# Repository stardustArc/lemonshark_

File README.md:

# lemonshark

a wireless split keyboard with per-key RGB and nice!view displays

---
## to do
- [ ] write readme (this is gonna take a lot of commits lol)
- [ ] upload images/gallery
- [ ] modify logo image to be cleaner (light mode jumpscare rn)
- [ ] create v2 PCB
- [ ] build guide?
- [ ] user-mods/cases (pyntie's case + plateless + OLED-compatible display cover)
- [ ] clean up ZMK config/readme/keymap (need to add link to this)

---

▲ lemonshark with plateless case, RGB, and MBK glow

---
## features:
- choc v1 compatible
- wireless
- nice!view-compatible displays
- per-key RGB
- extra-large battery

---
## ZMK config

need to clean up the [repo](https://github.com/stardustArc/zmk-config-lemonsharkv2) but here it is

---
## V1 BOM

| Part | Count | Desc | Source |
| ----------- | ----------- |----------- | ----------- |
| Left PCB | 1 | | Your preferred fab, or message me, there's always a chance I have spare boards |
| Right PCB | 1 | | same as above |
| nice!nano v2 | 2 | MCU, though any wireless Pro Micro-based MCU will work | [Typeractive (real)](https://typeractive.xyz/products/nice-nano) or [Amazon (clone)](https://www.amazon.com/Teyleten-Robot-Development-Bluetooth-Management/dp/B0CYLNZ6V4) |
| nice!view | 2 | display, vertical SSD1306 OLEDs are also compatible | [Typeractive (nice!view)](https://typeractive.xyz/products/nice-view) or [Amazon (OLED)](https://www.amazon.com/MakerFocus-Display-SSD1306-3-3V-5V-Arduino/dp/B079BN2J8V?th=1)
| Batteries | 1 | PS3 replacement batteries, comes in a 2pk | [Amazon](https://www.amazon.com/Replacement-Playstation-Controller-CECHZC2E-CECHZC2U-3/dp/B09726K2LC) |
| Choc V1 | 56 | switches, **choc V2 NOT compatible** | [Ambient Twilights](https://lowprokb.ca/collections/switches/products/ambients-silent-choc-switches?variant=44873426436260) you don't have to use these obviously, I just like them |
| Hotswap sockets | 56 | choc hotswap switches | [Amazon](https://www.amazon.com/Mechkeeb-Kailh-Low-Hot-swappable-Socket/dp/B0BS3JYJJQ?th=1) |
| 1N4148W SOD-123F | 56 | SMD diodes, buy spares (like 60) | [Digikey](https://www.digikey.com/en/products/detail/diotec-semiconductor/1N4148W/18833653) |
| EVQ-PUA02K | 2 | reset button | [Digikey](https://www.digikey.com/en/products/detail/panasonic-electronic-components/EVQ-PUA02K/286334) |
| SSSS811101 | 4 | power switch | [Digikey](https://www.digikey.com/en/products/detail/alps-alpine/SSSS811101/19529062) |
| S2B-PH-K-S | 2 | right angle male 2mm JST-PH connector| [Digikey](https://www.digikey.com/en/products/detail/jst-sales-america-inc/S2B-PH-K-S/926626) |
| Mill-Max 310-47-112-41-001000 | 5 | machine pin header for MCU and display | [Digikey](https://www.digikey.com/en/products/detail/mill-max-manufacturing-corp/310-47-112-41-001000/7364039) |
| Mill-Max 3320-0-00-15-00-00-03-0 | 65 | pins for headers, this count includes 7 spares | [Digikey](https://www.digikey.com/en/products/detail/mill-max-manufacturing-corp/3320-0-00-15-00-00-03-0/4147392) |
| Adafruit MiniBoost 5V TPS61023 | 2 | level shifter for LEDs | [Digikey](https://www.digikey.com/en/products/detail/adafruit-industries-llc/4654/12697636) |
| SK6812 Mini-E | 56 | LEDs, best to use SK6803 but it's not what I had, plus these were dirt cheap | [Amazon](https://www.amazon.com/Lizusidtsy-Similar-Individually-Addressable-500076361/dp/B0D62PYX62) |
| Keycaps of your choice | 56 | 54 1u keys, 2 1.5u keys. Choc-spaced | take your pick! MBK Legends Glow R1 for me |
| Case | 2 | one of each half | located in this repository |

---
## Credits

A massive thank you to the MrZealot and [Ceoloide](https://github.com/ceoloide) for creating and maintaining [Ergogen](https://ergogen.xyz), the software with which lemonshark was created. The [Absolem Club discord](http://discord.ergogen.xyz/) was irreplacable for help of all sorts, as was FlatFootFox with his [writeup](https://flatfootfox.com/ergogen-introduction/) on Ergogen. Additonally, thank you to car, Evelyn, [Peter](https://github.com/peterjc/), Fox, Turtlyn, and [Grinnie](https://github.com/regicidalplutophage) from Absolem Club, they were all a massive help in getting through this monumental project.

Thanks to Genteure and their [ZMK Shield Wizard](https://shield-wizard.genteure.workers.dev/), it made configuring ZMK a breeze. Also, thanks to the entire team behind the [ZMK firmware](https://zmk.dev), one of the main goals of this board wouldn't be possible without you.

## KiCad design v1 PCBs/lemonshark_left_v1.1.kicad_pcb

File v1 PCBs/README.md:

# V1 PCBs
---
V1 PCB and various files are now uploaded!

If you want to build your own lemonshark board, please use the V2 PCB (coming soon!). V1 currently has a few issues (various bodges and janky solutions) and is only uploaded for reference purposes.

**The build guide uses a V1 PCB** <- build guide coming soon
this is just because i don't have a V2 PCB on hand, and probably won't for a while. However, if and when I do obtain a V2 PCB, i will create another build guide for V2.

UPDATE: V1.1 PCBs uploaded, these have replaced V1. This eliminates bodges, but is still limited to running choc V1 only and LEDs through a level shifter

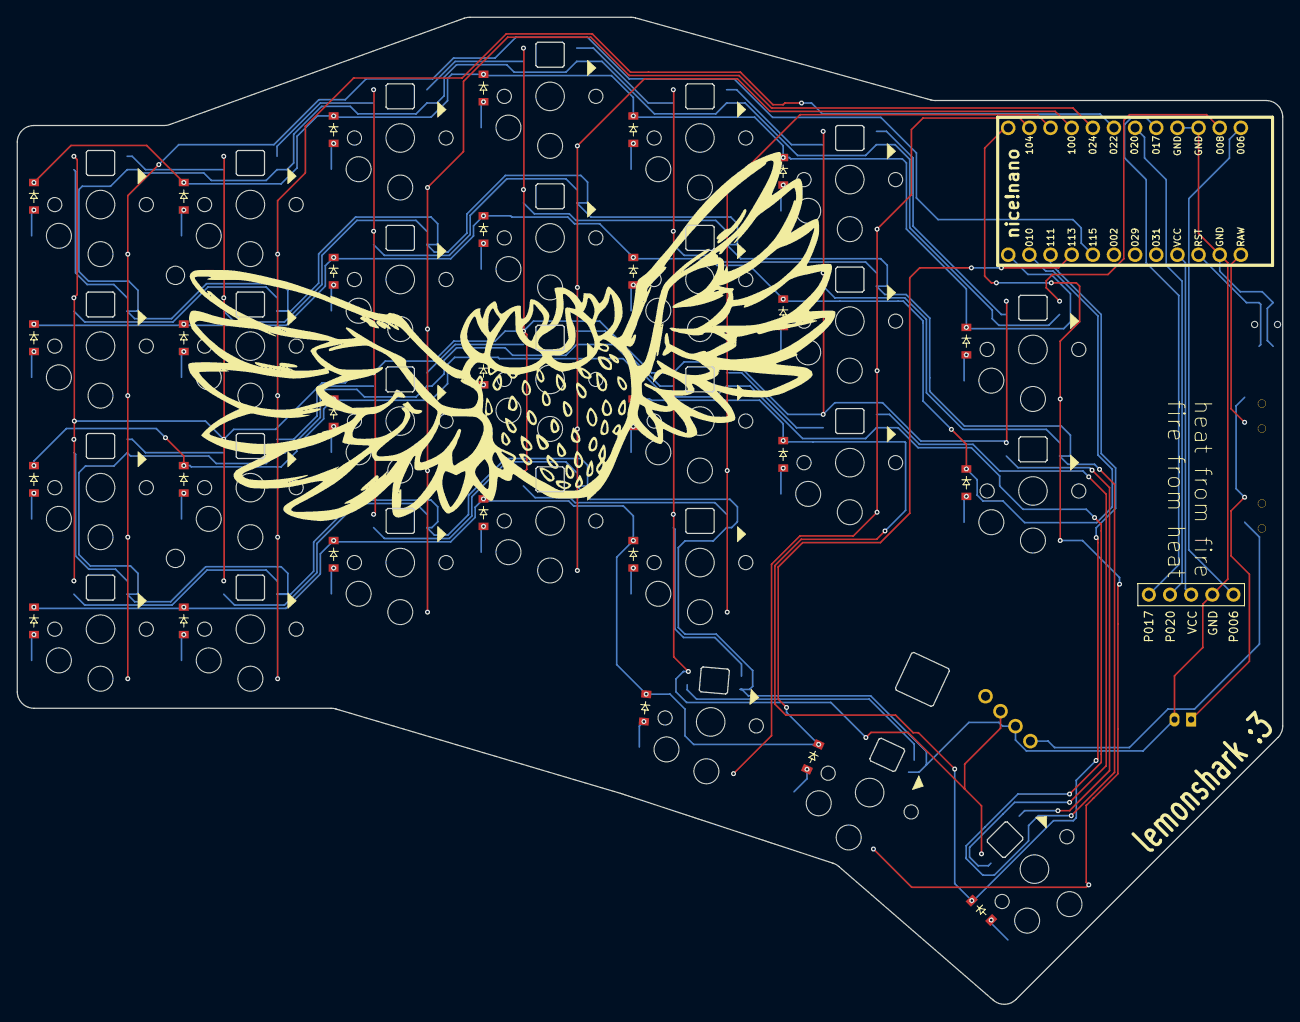
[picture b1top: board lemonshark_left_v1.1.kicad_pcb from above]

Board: 2 copper layers, 152.0 x 118.6 mm, 92 parts (0 on the bottom side), 50 nets.

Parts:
B1: Panasonic_EVQPUL_EVQPUC
D1, D2, D3, D4, D5, D6, D7, D8, D9, D10, D11, D12, D13, D14, D15, D16, D17, D18, D19, D20, D21, D22, D23, D24, D25, D26, D27, D28: ComboDiode
DISP1: display_nice_view
JST1: JST_PH_S2B-PH-K_02x2.00mm_Angled
LED1, LED2, LED3, LED4, LED5, LED6, LED7, LED8, LED9, LED10, LED11, LED12, LED13, LED14, LED15, LED16, LED17, LED18, LED19, LED20, LED21, LED22, LED23, LED24, LED25, LED26, LED27, LED28: WS2812B
MCU1: nice_nano
MH1, MH2: mounting_hole_npth
S1, S2, S3, S4, S5, S6, S7, S8, S9, S10, S11, S12, S13, S14, S15, S16, S17, S18, S19, S20, S21, S22, S23, S24, S25, S26, S27, S28: PG1350
T1, T2: SPDT_C128955

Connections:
5v: LED1.1, LED2.1, LED3.1, LED4.1, LED5.1, LED6.1, LED7.1, LED8.1, LED9.1, LED10.1, LED11.1, LED12.1, LED13.1, LED14.1, LED15.1, LED16.1, LED17.1, LED18.1, LED19.1, LED20.1, LED21.1, LED22.1, LED23.1, LED24.1, LED25.1, LED26.1, LED27.1, LED28.1
GND: B1.1, DISP1.4, JST1.2, LED1.3, LED2.3, LED3.3, LED4.3, LED5.3, LED6.3, LED7.3, LED8.3, LED9.3, LED10.3, LED11.3, LED12.3, LED13.3, LED14.3, LED15.3, LED16.3, LED17.3, LED18.3, LED19.3, LED20.3, LED21.3, LED22.3, LED23.3, LED24.3, LED25.3, LED26.3, LED27.3, LED28.3, MCU1.3, MCU1.4, MCU1.23
P006: DISP1.5, MCU1.1
P008: LED2.4, MCU1.2
P009: D2.1, D5.1, D9.1, D13.1, D17.1, D21.1, D25.1, MCU1.13
P010: D1.1, D4.1, D8.1, D12.1, D16.1, D20.1, D24.1, MCU1.14
P011: MCU1.10, S6.1, S7.1, S8.1, S9.1
P017: DISP1.1, MCU1.5
P020: DISP1.2, MCU1.6
P022: MCU1.7, S18.1, S19.1, S20.1, S21.1
P024: MCU1.8, S14.1, S15.1, S16.1, S17.1
P100: MCU1.9, S10.1, S11.1, S12.1, S13.1
P104: MCU1.11, S3.1, S4.1, S5.1, S28.1
P106: MCU1.12, S1.1, S2.1, S26.1, S27.1
P111: D3.1, D7.1, D11.1, D15.1, D19.1, D23.1, D26.1, MCU1.15
P113: D6.1, D10.1, D14.1, D18.1, D22.1, D27.1, D28.1, MCU1.16
P115: MCU1.17, S22.1, S23.1, S24.1, S25.1
RAW: MCU1.24, T1.2
RST: B1.2, MCU1.22
VCC: DISP1.3, MCU1.21
mirror_index_bottom: D6.2, S6.2
mirror_index_home: D7.2, S7.2
mirror_index_num: D9.2, S9.2
mirror_index_top: D8.2, S8.2
mirror_inner_home: D3.2, S3.2
mirror_inner_num: D5.2, S5.2
mirror_inner_top: D4.2, S4.2
mirror_left_mod: D27.2, S27.2
mirror_math_num: D2.2, S2.2
mirror_math_top: D1.2, S1.2
mirror_middle_bottom: D10.2, S10.2
mirror_middle_home: D11.2, S11.2
mirror_middle_num: D13.2, S13.2
mirror_middle_top: D12.2, S12.2
mirror_outer_bottom: D22.2, S22.2
mirror_outer_home: D23.2, S23.2
mirror_outer_num: D25.2, S25.2
mirror_outer_top: D24.2, S24.2
mirror_pinky_bottom: D18.2, S18.2
mirror_pinky_home: D19.2, S19.2
mirror_pinky_num: D21.2, S21.2
mirror_pinky_top: D20.2, S20.2
mirror_right_mod: D28.2, S28.2
mirror_ring_bottom: D14.2, S14.2
mirror_ring_home: D15.2, S15.2
mirror_ring_num: D17.2, S17.2
mirror_ring_top: D16.2, S16.2
mirror_space_mod: D26.2, S26.2
pos: JST1.1, T1.1, T2.1
undefined: LED1.2, LED1.4, LED2.2, LED3.2, LED3.4, LED4.2, LED4.4, LED5.2, LED5.4, LED6.2, LED6.4, LED7.2, LED7.4, LED8.2, LED8.4, LED9.2, LED9.4, LED10.2, LED10.4, LED11.2, LED11.4, LED12.2, LED12.4, LED13.2, LED13.4, LED14.2, LED14.4, LED15.2, LED15.4, LED16.2, LED16.4, LED17.2, LED17.4, LED18.2, LED18.4, LED19.2, LED19.4, LED20.2, LED20.4, LED21.2, LED21.4, LED22.2, LED22.4, LED23.2, LED23.4, LED24.2, LED24.4, LED25.2, LED25.4, LED26.2, LED26.4, LED27.2, LED27.4, LED28.2, LED28.4

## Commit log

2026-02-28 Update README.md
    testing stuff, more later
2026-03-27 Update README.md goals
    added goals to readme
2026-03-27 Create user-mods
2026-03-27 Update user-mods
2026-03-27 Create user-mods README
2026-03-27 Create V1 PCBs README
2026-04-19 Create photos.md
    created photos folder, need to add photos
2026-04-19 Update README.md
    added feature list, updated todo
2026-04-19 added images + logo
    uploaded photoshoot images and logo
2026-04-19 Rename DSC_6427.JPG to left_RGB.JPG
2026-04-19 Delete photos/left_RGB.JPG
    accidentally deleted photo, reuploading
2026-04-19 Update README.md
    added logo, converted todo to a checklist, modified feature list, created credits
2026-04-19 Update README.md
    fixed a mistake in credits
2026-04-19 Update README.md
    fixed logo (hopefully)
2026-04-19 Update README.md
    added main photos, updated todo
2026-04-19 Update README.md
    rearranged stuff, yet more todo updates
2026-04-19 Update README.md
    fixed todo not actually being a markdown task list
2026-04-24 added v1 PCB files
2026-04-24 Create gerbers
2026-04-24 Create files
2026-04-24 added ergogen config
2026-04-24 added footprints
2026-04-24 Update README.md
    added BOM (i hope the formatting is right), messed with credits
2026-04-30 uploaded v1.1 files
2026-04-30 added v1.1 gerbers
